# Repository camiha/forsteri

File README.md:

# forsteri
 40%, alice-style keyboard   

type-a

type-b(progress)

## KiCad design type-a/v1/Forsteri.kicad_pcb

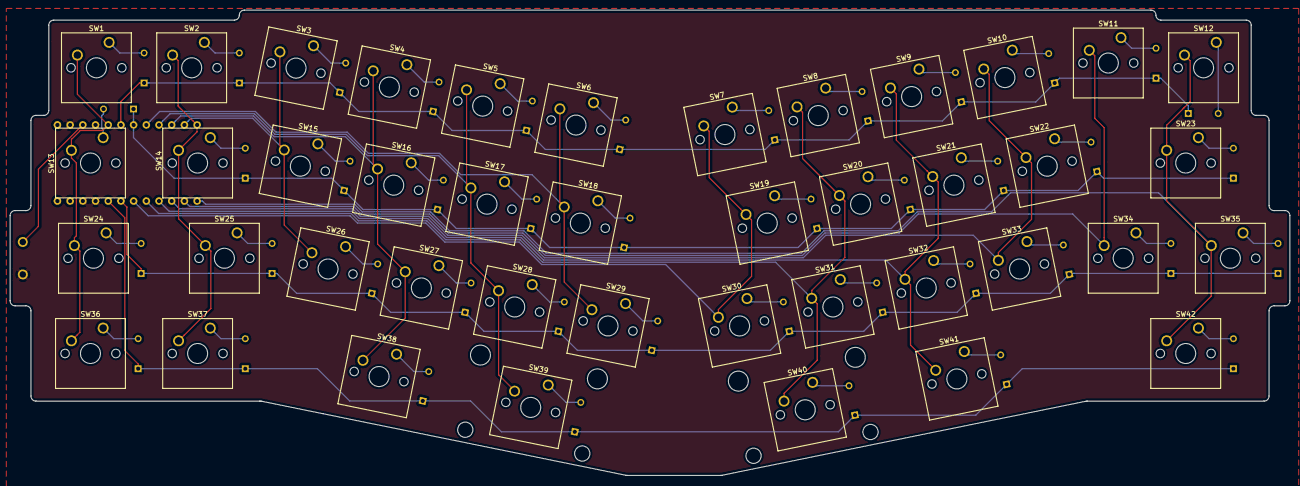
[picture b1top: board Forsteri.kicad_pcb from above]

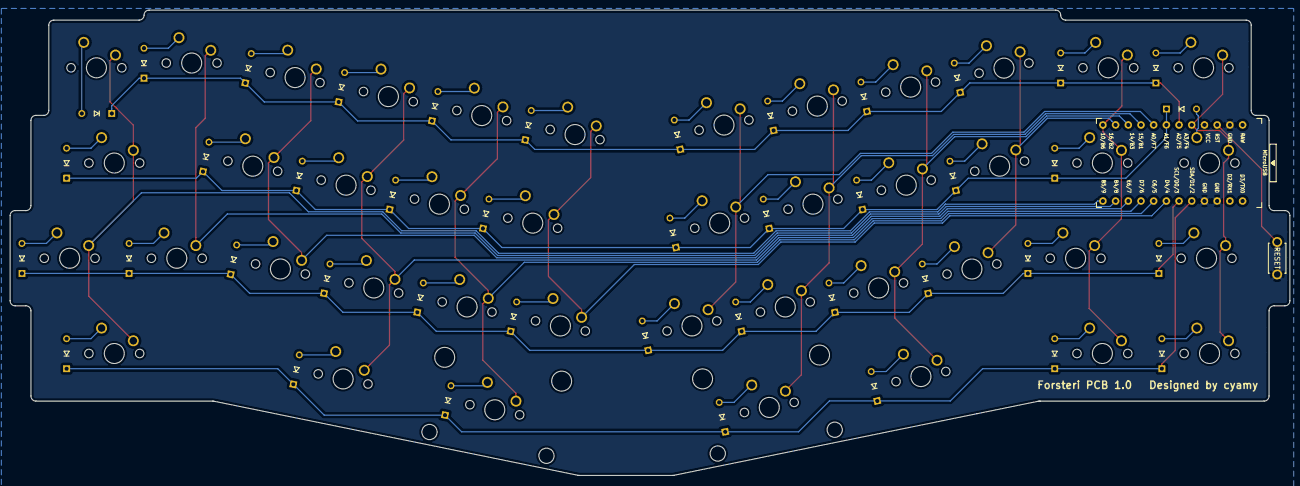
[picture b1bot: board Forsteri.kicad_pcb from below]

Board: 2 copper layers, 256.0 x 93.1 mm, 86 parts (44 on the bottom side), 60 nets.

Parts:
D1, D2, D3, D4, D5, D6, D7, D8, D9, D10, D11, D12, D13, D14, D15, D16, D17, D18, D19, D20, D21, D22, D23, D24, D25, D26, D27, D28, D29, D30, D31, D32, D33, D34, D35, D36, D37, D38, D39, D40, D41, D42: D_Small; D3_TH
SW1, SW2, SW3, SW4, SW5, SW6, SW7, SW8, SW9, SW10, SW11, SW12, SW14, SW15, SW16, SW17, SW18, SW19, SW20, SW21, SW22, SW25, SW26, SW27, SW28, SW29, SW30, SW31, SW32, SW33, SW34, SW37, SW38: SW_PUSH; SW_Cherry_MX_1.00u_PCB
SW13, SW35, SW36, SW41: SW_PUSH; SW_Cherry_MX_1.25u_PCB
SW23, SW24, SW42: SW_PUSH; SW_Cherry_MX_1.75u_PCB
SW39: SW_PUSH; SW_Cherry_MX_2.25u_PCB_ReverseStabilizer
SW40: SW_PUSH; SW_Cherry_MX_2.00u_PCB_ReverseStabilizer
SW43: SW_PUSH; ResetSW_1side
U1: ProMicro; ProMicro_v3

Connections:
GND: SW43.2, U1.3, U1.4, U1.23
unnamed: D1.2, SW1.1
unnamed: D2.2, SW2.1
unnamed: D3.2, SW3.1
unnamed: D4.2, SW4.1
unnamed: D5.2, SW5.1
unnamed: D6.2, SW6.1
unnamed: D7.2, SW7.1
unnamed: D8.2, SW8.1
unnamed: D9.2, SW9.1
unnamed: D10.2, SW10.1
unnamed: D11.2, SW11.1
unnamed: D12.2, SW12.1
unnamed: D13.2, SW13.1
unnamed: D14.2, SW14.1
unnamed: D15.2, SW15.1
unnamed: D16.2, SW16.1
unnamed: D17.2, SW17.1
unnamed: D18.2, SW18.1
unnamed: D19.2, SW19.1
unnamed: D20.2, SW20.1
unnamed: D21.2, SW21.1
unnamed: D22.2, SW22.1
unnamed: D23.2, SW23.1
unnamed: D24.2, SW24.1
unnamed: D25.2, SW25.1
unnamed: D26.2, SW26.1
unnamed: D27.2, SW27.1
unnamed: D28.2, SW28.1
unnamed: D29.2, SW29.1
unnamed: D30.2, SW30.1
unnamed: D31.2, SW31.1
unnamed: D32.2, SW32.1
unnamed: D33.2, SW33.1
unnamed: D34.2, SW34.1
unnamed: D35.2, SW35.1
unnamed: D36.2, SW36.1
unnamed: D37.2, SW37.1
unnamed: D38.2, SW38.1
unnamed: D39.2, SW39.1
unnamed: D40.2, SW40.1
unnamed: D41.2, SW41.1
unnamed: D42.2, SW42.1
unnamed: SW43.1, U1.22
col0: SW1.2, SW13.2, SW24.2, SW36.2, U1.20
col1: SW2.2, SW14.2, SW25.2, SW37.2, U1.13
col2: SW3.2, SW15.2, SW26.2, U1.14
col3: SW4.2, SW16.2, SW27.2, SW38.2, U1.15
col4: SW5.2, SW17.2, SW28.2, SW39.2, U1.16
col5: SW6.2, SW18.2, SW29.2, U1.17
col6: SW7.2, SW19.2, SW30.2, U1.7
col7: SW8.2, SW20.2, SW31.2, SW40.2, U1.8
col8: SW9.2, SW21.2, SW32.2, SW41.2, U1.9
col9: SW10.2, SW22.2, SW33.2, U1.10
col10: SW11.2, SW34.2, U1.11
col11: SW12.2, SW23.2, SW35.2, SW42.2, U1.12
row0: D1.1, D2.1, D3.1, D4.1, D5.1, D6.1, D7.1, D8.1, D9.1, D10.1, D11.1, D12.1, U1.19
row1: D13.1, D14.1, D15.1, D16.1, D17.1, D18.1, D19.1, D20.1, D21.1, D22.1, D23.1, U1.18
row2: D24.1, D25.1, D26.1, D27.1, D28.1, D29.1, D30.1, D31.1, D32.1, D33.1, D34.1, D35.1, U1.6
row3: D36.1, D37.1, D38.1, D39.1, D40.1, D41.1, D42.1, U1.5

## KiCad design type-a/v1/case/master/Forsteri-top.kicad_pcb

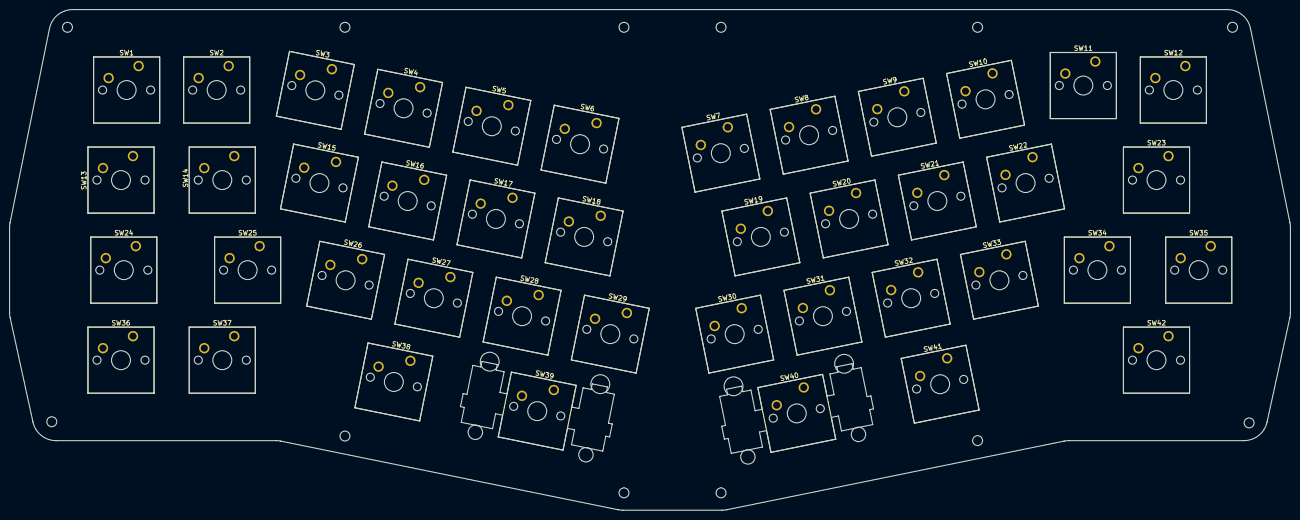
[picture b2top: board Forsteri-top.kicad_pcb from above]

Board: 2 copper layers, 271.0 x 105.9 mm, 42 parts (0 on the bottom side), 12 nets, no tracks yet.

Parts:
SW1, SW2, SW3, SW4, SW5, SW6, SW7, SW8, SW9, SW10, SW11, SW12, SW14, SW15, SW16, SW17, SW18, SW19, SW20, SW21, SW22, SW25, SW26, SW27, SW28, SW29, SW30, SW31, SW32, SW33, SW34, SW37, SW38: SW_PUSH; SW_Cherry_MX_1.00u_PCB
SW13, SW35, SW36, SW41: SW_PUSH; SW_Cherry_MX_1.25u_PCB
SW23, SW24, SW42: SW_PUSH; SW_Cherry_MX_1.75u_PCB
SW39: SW_PUSH; SW_Cherry_MX_2.25u_PCB_ReverseStabilizer
SW40: SW_PUSH; SW_Cherry_MX_2.00u_PCB_ReverseStabilizer

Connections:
col0: SW1.2, SW13.2, SW24.2, SW36.2
col1: SW2.2, SW14.2, SW25.2, SW37.2
col2: SW3.2, SW15.2, SW26.2
col3: SW4.2, SW16.2, SW27.2, SW38.2
col4: SW5.2, SW17.2, SW28.2, SW39.2
col5: SW6.2, SW18.2, SW29.2
col6: SW7.2, SW19.2, SW30.2
col7: SW8.2, SW20.2, SW31.2, SW40.2
col8: SW9.2, SW21.2, SW32.2, SW41.2
col9: SW10.2, SW22.2, SW33.2
col10: SW11.2, SW34.2
col11: SW12.2, SW23.2, SW35.2, SW42.2
